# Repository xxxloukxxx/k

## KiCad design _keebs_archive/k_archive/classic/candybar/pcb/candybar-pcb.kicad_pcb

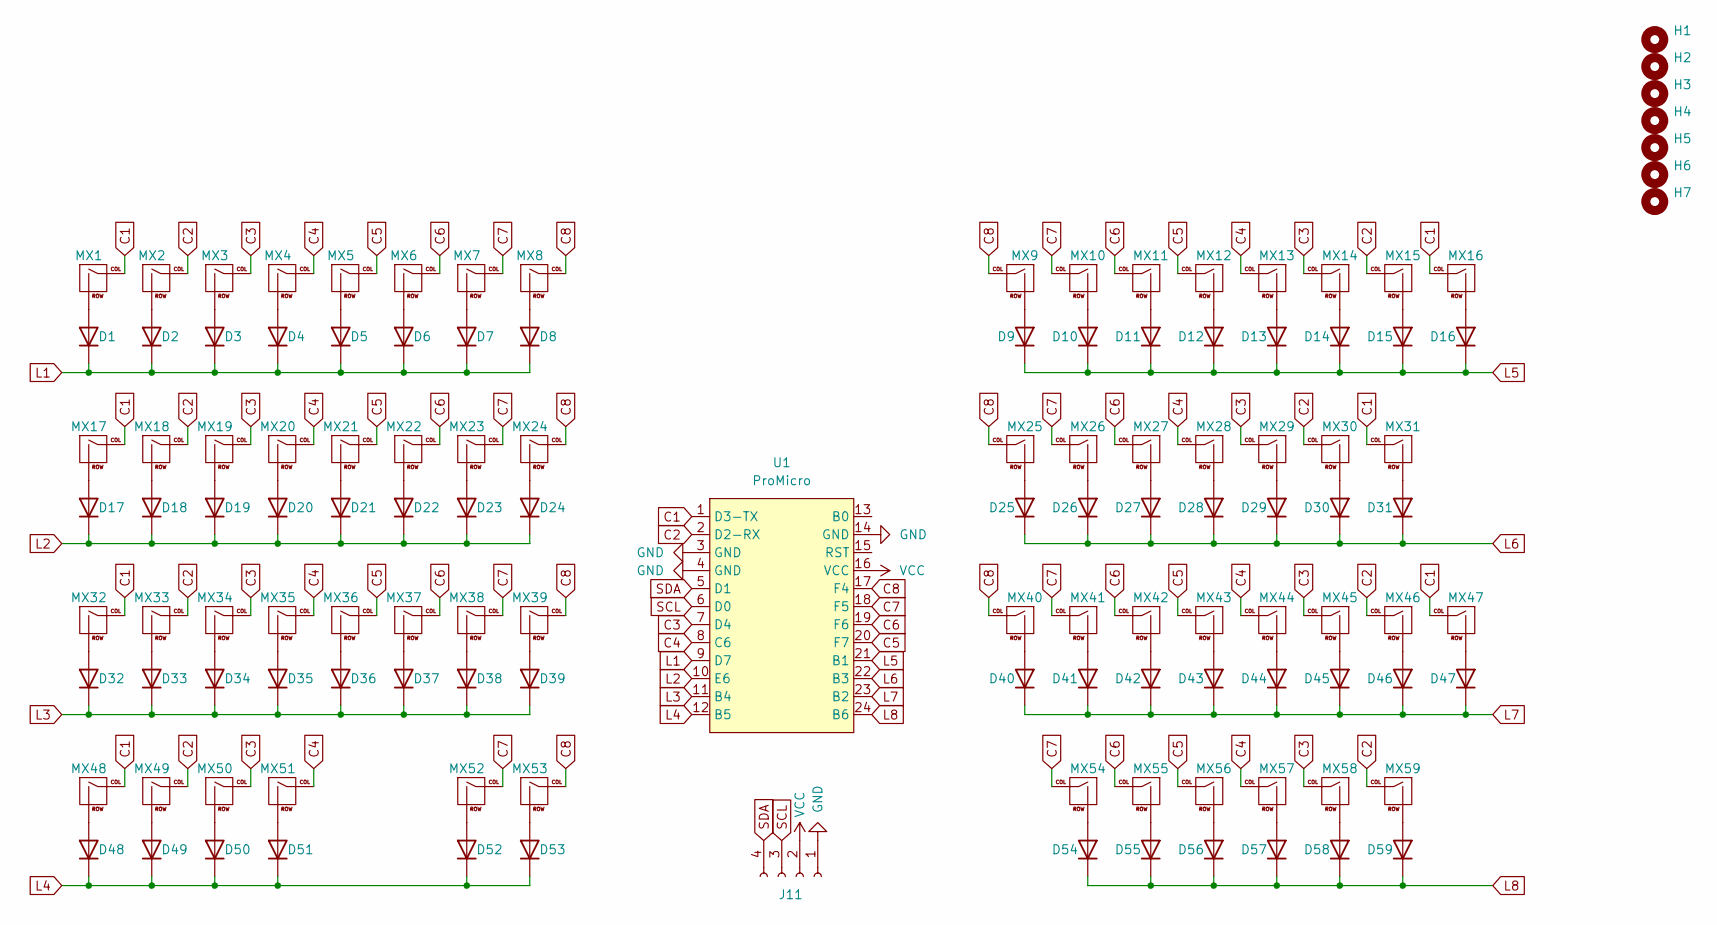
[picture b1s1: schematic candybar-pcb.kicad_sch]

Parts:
D1, D2, D3, D4, D5, D6, D7, D8, D9, D10, D11, D12, D13, D14, D15, D16, D17, D18, D19, D20, D21, D22, D23, D24, D25, D26, D27, D28, D29, D30, D31, D32, D33, D34, D35, D36, D37, D38, D39, D40, D41, D42, D43, D44, D45, D46, D47, D48, D49, D50, D51, D52, D53, D54, D55, D56, D57, D58, D59: 1N4148; D_DO-35_SOD27_P7.62mm_Horizontal
H1, H2, H3, H4, H5, H6, H7: MountingHole; MountingHole_2.2mm_M2
J11: Conn_01x04_Socket; SSD1306-0.91-OLED-4pin-128x32
MX1, MX2, MX3, MX4, MX5, MX6, MX7, MX8, MX9, MX10, MX11, MX12, MX13, MX14, MX15, MX16, MX18, MX19, MX20, MX21, MX22, MX23, MX24, MX25, MX26, MX28, MX29, MX30, MX31, MX33, MX34, MX35, MX36, MX37, MX38, MX39, MX40, MX41, MX43, MX44, MX45, MX46, MX49, MX55, MX56, MX57, MX58, MX59: MX; MX-Alps-Hybrid-1U
MX17, MX42, MX48, MX50, MX53, MX54: MX; MX-Alps-Hybrid-1.25U
MX27, MX32: MX; MX-Alps-Hybrid-1.75U
MX47: MX; MX-Alps-Hybrid-2U-Vertical
MX51: MX; MX-Alps-Hybrid-2.75U-ReversedStabilizers
MX52: MX; MX-Alps-Hybrid-2.25U-ReversedStabilizers
U1: ProMicro; ProMicro_USBup

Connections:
C1: MX1.1 (COL), MX16.1 (COL), MX17.1 (COL), MX31.1 (COL), MX32.1 (COL), MX47.1 (COL), MX48.1 (COL), U1.1 (D3-TX)
C2: MX2.1 (COL), MX15.1 (COL), MX18.1 (COL), MX30.1 (COL), MX33.1 (COL), MX46.1 (COL), MX49.1 (COL), MX59.1 (COL), U1.2 (D2-RX)
C3: MX3.1 (COL), MX14.1 (COL), MX19.1 (COL), MX29.1 (COL), MX34.1 (COL), MX45.1 (COL), MX50.1 (COL), MX58.1 (COL), U1.7 (D4)
C4: MX4.1 (COL), MX13.1 (COL), MX20.1 (COL), MX28.1 (COL), MX35.1 (COL), MX44.1 (COL), MX51.1 (COL), MX57.1 (COL), U1.8 (C6)
C5: MX5.1 (COL), MX12.1 (COL), MX21.1 (COL), MX36.1 (COL), MX43.1 (COL), MX56.1 (COL), U1.20 (F7)
C6: MX6.1 (COL), MX11.1 (COL), MX22.1 (COL), MX27.1 (COL), MX37.1 (COL), MX42.1 (COL), MX55.1 (COL), U1.19 (F6)
C7: MX7.1 (COL), MX10.1 (COL), MX23.1 (COL), MX26.1 (COL), MX38.1 (COL), MX41.1 (COL), MX52.1 (COL), MX54.1 (COL), U1.18 (F5)
C8: MX8.1 (COL), MX9.1 (COL), MX24.1 (COL), MX25.1 (COL), MX39.1 (COL), MX40.1 (COL), MX53.1 (COL), U1.17 (F4)
GND: J11.1, U1.3 (GND), U1.4 (GND), U1.14 (GND)
L1: D1.1 (K), D2.1 (K), D3.1 (K), D4.1 (K), D5.1 (K), D6.1 (K), D7.1 (K), D8.1 (K), U1.9 (D7)
L2: D17.1 (K), D18.1 (K), D19.1 (K), D20.1 (K), D21.1 (K), D22.1 (K), D23.1 (K), D24.1 (K), U1.10 (E6)
L3: D32.1 (K), D33.1 (K), D34.1 (K), D35.1 (K), D36.1 (K), D37.1 (K), D38.1 (K), D39.1 (K), U1.11 (B4)
L4: D48.1 (K), D49.1 (K), D50.1 (K), D51.1 (K), D52.1 (K), D53.1 (K), U1.12 (B5)
L5: D9.1 (K), D10.1 (K), D11.1 (K), D12.1 (K), D13.1 (K), D14.1 (K), D15.1 (K), D16.1 (K), U1.21 (B1)
L6: D25.1 (K), D26.1 (K), D27.1 (K), D28.1 (K), D29.1 (K), D30.1 (K), D31.1 (K), U1.22 (B3)
L7: D40.1 (K), D41.1 (K), D42.1 (K), D43.1 (K), D44.1 (K), D45.1 (K), D46.1 (K), D47.1 (K), U1.23 (B2)
L8: D54.1 (K), D55.1 (K), D56.1 (K), D57.1 (K), D58.1 (K), D59.1 (K), U1.24 (B6)
unnamed: D1.2 (A), MX1.2 (ROW)
unnamed: D2.2 (A), MX2.2 (ROW)
unnamed: D3.2 (A), MX3.2 (ROW)
unnamed: D4.2 (A), MX4.2 (ROW)
unnamed: D5.2 (A), MX5.2 (ROW)
unnamed: D6.2 (A), MX6.2 (ROW)
unnamed: D7.2 (A), MX7.2 (ROW)
unnamed: D8.2 (A), MX8.2 (ROW)
unnamed: D9.2 (A), MX9.2 (ROW)
unnamed: D10.2 (A), MX10.2 (ROW)
unnamed: D11.2 (A), MX11.2 (ROW)
unnamed: D12.2 (A), MX12.2 (ROW)
unnamed: D13.2 (A), MX13.2 (ROW)
unnamed: D14.2 (A), MX14.2 (ROW)
unnamed: D15.2 (A), MX15.2 (ROW)
unnamed: D16.2 (A), MX16.2 (ROW)
unnamed: D17.2 (A), MX17.2 (ROW)
unnamed: D18.2 (A), MX18.2 (ROW)
unnamed: D19.2 (A), MX19.2 (ROW)
unnamed: D20.2 (A), MX20.2 (ROW)
unnamed: D21.2 (A), MX21.2 (ROW)
unnamed: D22.2 (A), MX22.2 (ROW)
unnamed: D23.2 (A), MX23.2 (ROW)
unnamed: D24.2 (A), MX24.2 (ROW)
unnamed: D25.2 (A), MX25.2 (ROW)
unnamed: D26.2 (A), MX26.2 (ROW)
unnamed: D27.2 (A), MX27.2 (ROW)
unnamed: D28.2 (A), MX28.2 (ROW)
unnamed: D29.2 (A), MX29.2 (ROW)
unnamed: D30.2 (A), MX30.2 (ROW)
unnamed: D31.2 (A), MX31.2 (ROW)
unnamed: D32.2 (A), MX32.2 (ROW)
unnamed: D33.2 (A), MX33.2 (ROW)
unnamed: D34.2 (A), MX34.2 (ROW)
unnamed: D35.2 (A), MX35.2 (ROW)
unnamed: D36.2 (A), MX36.2 (ROW)
unnamed: D37.2 (A), MX37.2 (ROW)
unnamed: D38.2 (A), MX38.2 (ROW)
unnamed: D39.2 (A), MX39.2 (ROW)
unnamed: D40.2 (A), MX40.2 (ROW)
unnamed: D41.2 (A), MX41.2 (ROW)
unnamed: D42.2 (A), MX42.2 (ROW)
unnamed: D43.2 (A), MX43.2 (ROW)
unnamed: D44.2 (A), MX44.2 (ROW)
unnamed: D45.2 (A), MX45.2 (ROW)
unnamed: D46.2 (A), MX46.2 (ROW)
unnamed: D47.2 (A), MX47.2 (ROW)
unnamed: D48.2 (A), MX48.2 (ROW)
unnamed: D49.2 (A), MX49.2 (ROW)
unnamed: D50.2 (A), MX50.2 (ROW)
unnamed: D51.2 (A), MX51.2 (ROW)
unnamed: D52.2 (A), MX52.2 (ROW)
unnamed: D53.2 (A), MX53.2 (ROW)
unnamed: D54.2 (A), MX54.2 (ROW)
unnamed: D55.2 (A), MX55.2 (ROW)
unnamed: D56.2 (A), MX56.2 (ROW)
unnamed: D57.2 (A), MX57.2 (ROW)
unnamed: D58.2 (A), MX58.2 (ROW)
unnamed: D59.2 (A), MX59.2 (ROW)
SCL: J11.3, U1.6 (D0)
SDA: J11.4, U1.5 (D1)
VCC: J11.2, U1.16 (VCC)

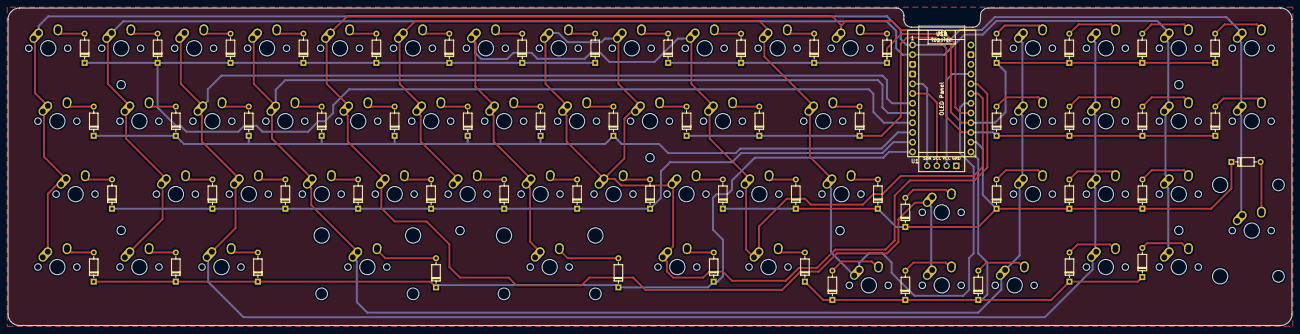
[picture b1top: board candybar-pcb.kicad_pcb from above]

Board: 2 copper layers, 335.3 x 82.9 mm, 127 parts (0 on the bottom side), 79 nets.

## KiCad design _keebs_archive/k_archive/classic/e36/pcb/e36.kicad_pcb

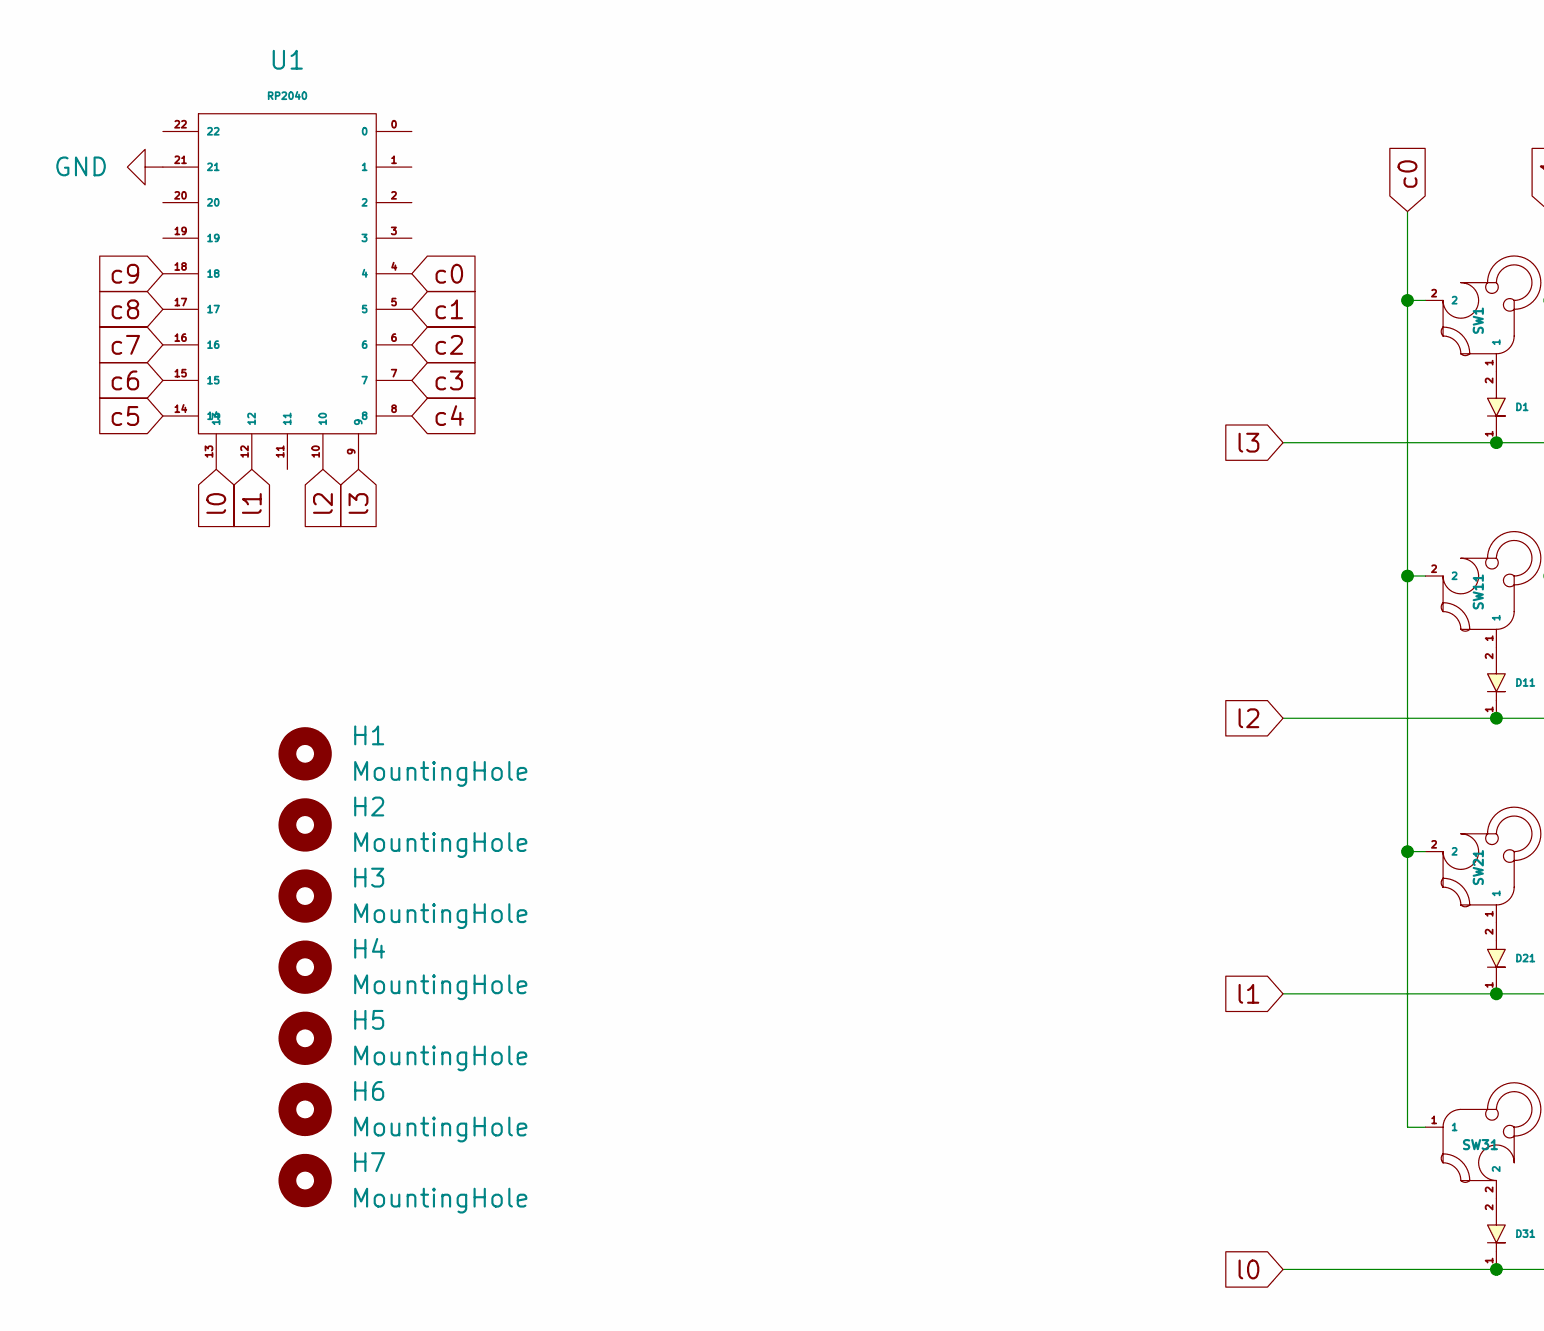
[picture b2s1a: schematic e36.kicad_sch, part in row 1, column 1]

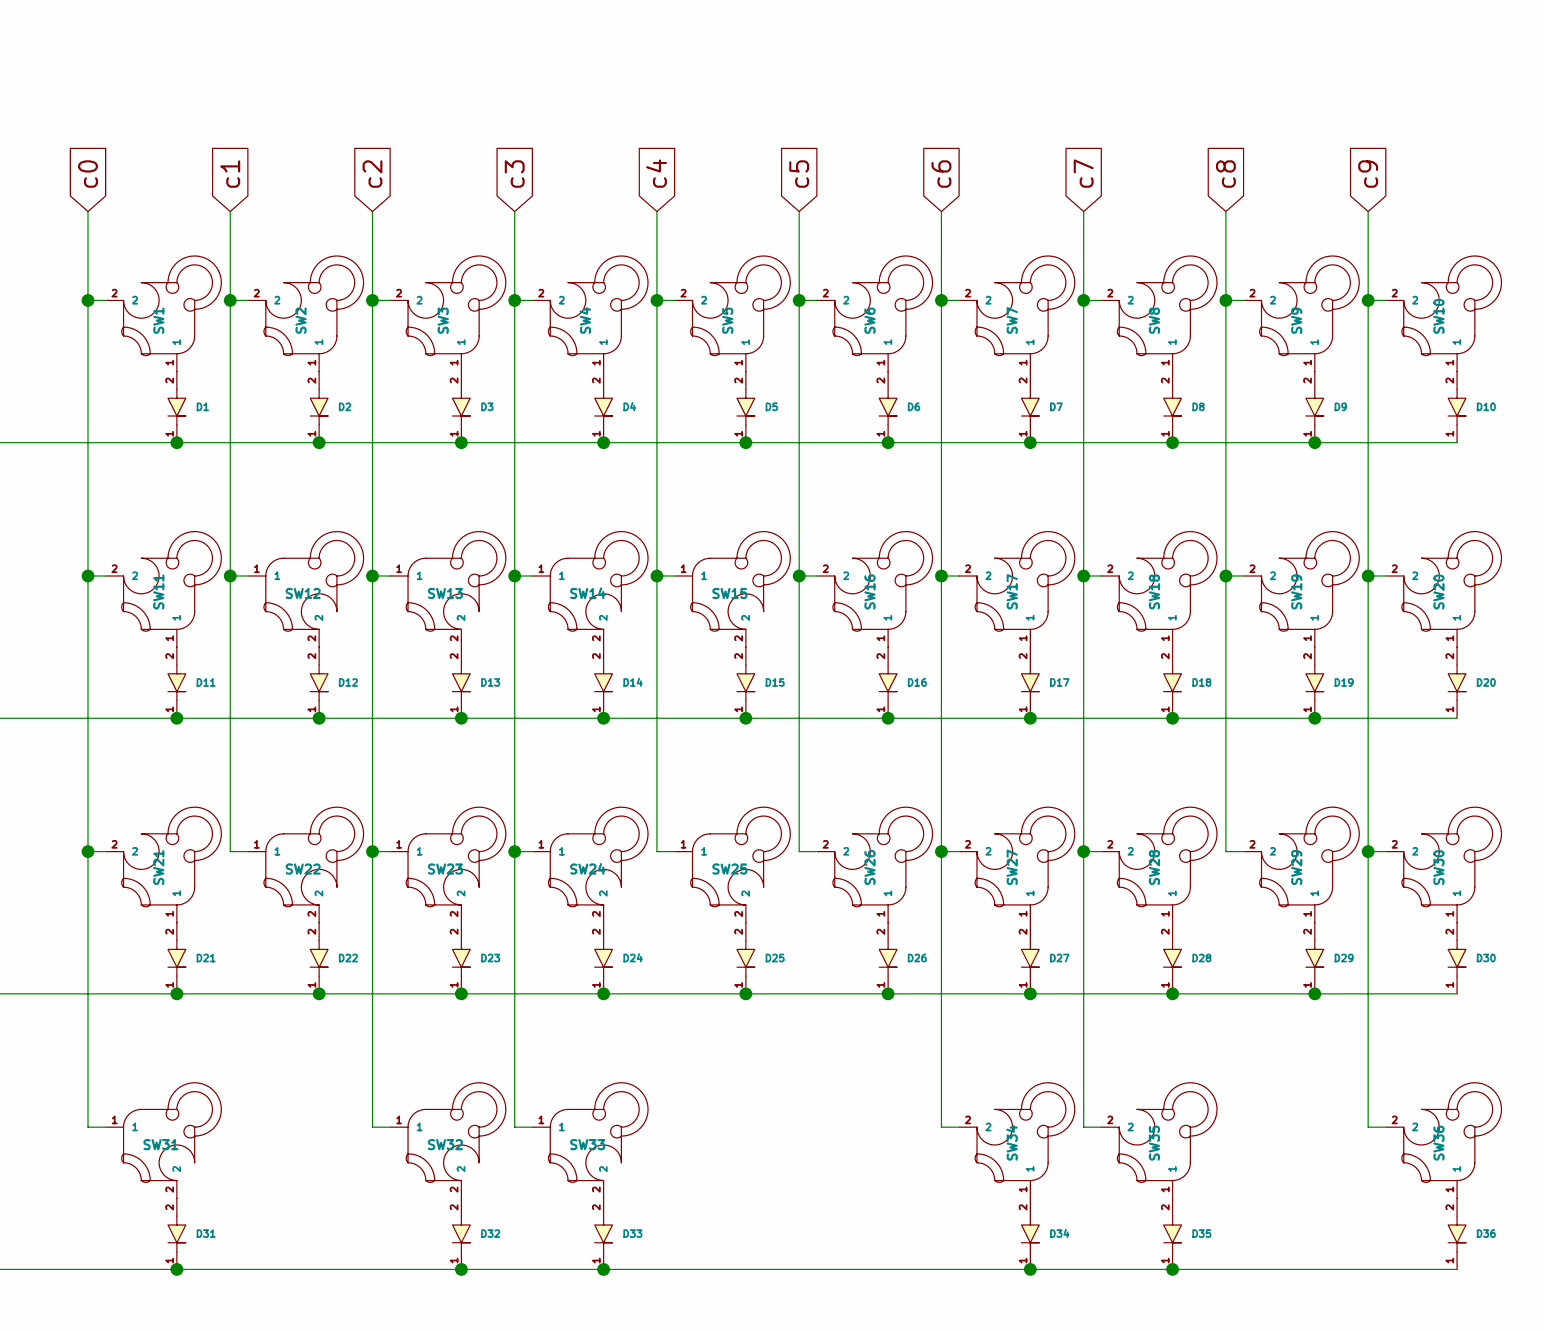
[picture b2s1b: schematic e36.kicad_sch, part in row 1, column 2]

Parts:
D1, D2, D3, D4, D5, D6, D7, D8, D9, D10, D11, D12, D13, D14, D15, D16, D17, D18, D19, D20, D21, D22, D23, D24, D25, D26, D27, D28, D29, D30, D31, D32, D33, D34, D35, D36: Diode
H1, H2, H3, H4, H5, H6, H7: MountingHole; MountingHole_2.2mm_M2
SW1, SW2, SW3, SW4, SW5, SW6, SW7, SW8, SW9, SW10, SW11, SW12, SW13, SW14, SW15, SW16, SW17, SW18, SW19, SW20, SW21, SW22, SW23, SW24, SW25, SW26, SW27, SW28, SW29, SW30, SW31, SW32, SW35, SW36: key; MX-5pin
SW33, SW34: key; MX-5pin_stab
U1: RP2040

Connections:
GND: U1.21
unnamed: D1.2, SW1.1
unnamed: D2.2, SW2.1
unnamed: D3.2, SW3.1
unnamed: D4.2, SW4.1
unnamed: D5.2, SW5.1
unnamed: D6.2, SW6.1
unnamed: D7.2, SW7.1
unnamed: D8.2, SW8.1
unnamed: D9.2, SW9.1
unnamed: D10.2, SW10.1
unnamed: D11.2, SW11.1
unnamed: D12.2, SW12.2
unnamed: D13.2, SW13.2
unnamed: D14.2, SW14.2
unnamed: D15.2, SW15.2
unnamed: D16.2, SW16.1
unnamed: D17.2, SW17.1
unnamed: D18.2, SW18.1
unnamed: D19.2, SW19.1
unnamed: D20.2, SW20.1
unnamed: D21.2, SW21.1
unnamed: D22.2, SW22.2
unnamed: D23.2, SW23.2
unnamed: D24.2, SW24.2
unnamed: D25.2, SW25.2
unnamed: D26.2, SW26.1
unnamed: D27.2, SW27.1
unnamed: D28.2, SW28.1
unnamed: D29.2, SW29.1
unnamed: D30.2, SW30.1
unnamed: D31.2, SW31.2
unnamed: D32.2, SW32.2
unnamed: D33.2, SW33.2
unnamed: D34.2, SW34.1
unnamed: D35.2, SW35.1
unnamed: D36.2, SW36.1
c0: SW1.2, SW11.2, SW21.2, SW31.1, U1.4
c1: SW2.2, SW12.1, SW22.1, U1.5
c2: SW3.2, SW13.1, SW23.1, SW32.1, U1.6
c3: SW4.2, SW14.1, SW24.1, SW33.1, U1.7
c4: SW5.2, SW15.1, SW25.1, U1.8
c5: SW6.2, SW16.2, SW26.2, U1.14
c6: SW7.2, SW17.2, SW27.2, SW34.2, U1.15
c7: SW8.2, SW18.2, SW28.2, SW35.2, U1.16
c8: SW9.2, SW19.2, SW29.2, U1.17
c9: SW10.2, SW20.2, SW30.2, SW36.2, U1.18
l0: D31.1, D32.1, D33.1, D34.1, D35.1, D36.1, U1.13
l1: D21.1, D22.1, D23.1, D24.1, D25.1, D26.1, D27.1, D28.1, D29.1, D30.1, U1.12
l2: D11.1, D12.1, D13.1, D14.1, D15.1, D16.1, D17.1, D18.1, D19.1, D20.1, U1.10
l3: D1.1, D2.1, D3.1, D4.1, D5.1, D6.1, D7.1, D8.1, D9.1, D10.1, U1.9

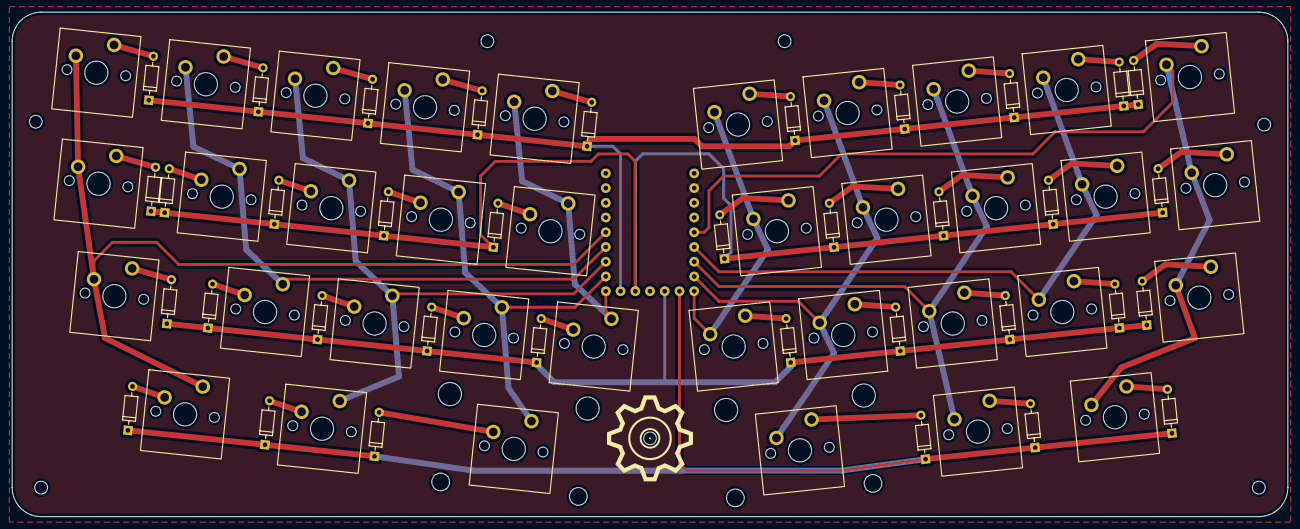
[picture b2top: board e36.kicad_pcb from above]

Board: 2 copper layers, 220.0 x 87.0 mm, 80 parts (1 on the bottom side), 50 nets.

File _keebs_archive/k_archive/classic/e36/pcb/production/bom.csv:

Designator,Footprint,Quantity,Value,LCSC Part #
"D1, D10, D11, D12, D13, D14, D15, D16, D17, D18, D19, D2, D20, D21, D22, D23, D24, D25, D26, D27, D28, D29, D3, D30, D31, D32, D33, D34, D35, D36, D4, D5, D6, D7, D8, D9",Diode,36,Diode,
"H1, H2, H3, H4, H5, H6, H7",MountingHole_2.2mm_M2,7,MountingHole,
"SW1, SW10, SW11, SW12, SW13, SW14, SW15, SW16, SW17, SW18, SW19, SW2, SW20, SW21, SW22, SW23, SW24, SW25, SW26, SW27, SW28, SW29, SW3, SW30, SW31, SW32, SW35, SW36, SW4, SW5, SW6, SW7, SW8, SW9",MX-5pin,34,key,
"SW33, SW34",MX-5pin_stab,2,key,
U1,RP2040,1,RP2040,

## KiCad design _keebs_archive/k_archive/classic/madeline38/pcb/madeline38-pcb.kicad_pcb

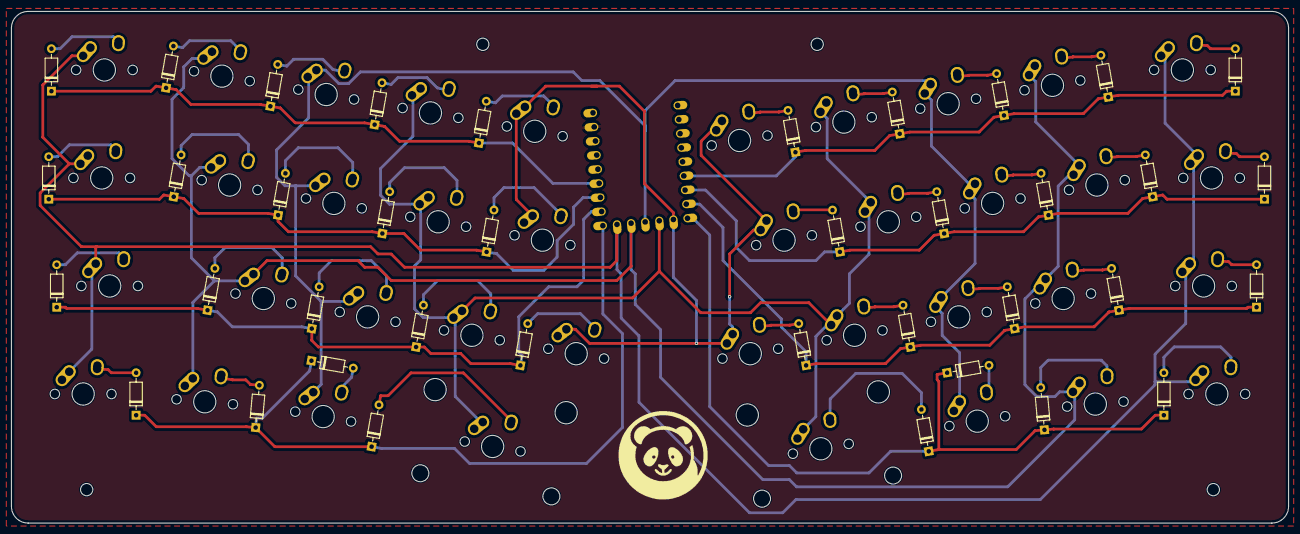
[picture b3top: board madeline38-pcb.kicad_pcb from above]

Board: 2 copper layers, 229.1 x 91.8 mm, 81 parts (0 on the bottom side), 51 nets.

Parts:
D1, D2, D3, D4, D5, D6, D7, D8, D9, D10, D11, D12, D13, D14, D15, D16, D17, D18, D19, D20, D21, D22, D23, D24, D25, D26, D27, D28, D29, D30, D31, D32, D33, D34, D35, D36, D37, D38: 1N4148; D_DO-35_SOD27_P7.62mm_Horizontal
H1, H2, H3, H4: MountingHole; MountingHole_2.2mm_M2
SW1, SW2, SW3, SW4, SW5, SW6, SW7, SW8, SW9, SW12, SW13, SW14, SW15, SW16, SW17, SW18, SW19, SW20, SW22, SW23, SW24, SW25, SW26, SW27, SW28, SW29, SW31, SW32, SW33, SW36, SW37, SW38: SW_SPST; MX-Alps-Hybrid-1U
SW10, SW11: SW_SPST; MX-Alps-Hybrid-1.25U
SW21: SW_SPST; MX-Alps-Hybrid-1.75U
SW30: SW_SPST; MX-Alps-Hybrid-1.5U
SW34: SW_SPST; MX-Alps-Hybrid-2.25U-ReversedStabilizers
SW35: SW_SPST; MX-Alps-Hybrid-2U-ReversedStabilizers
U1: rp2040-zero; rp2040-zero-tht

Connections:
unnamed: D1.2 (A), SW1.2 (B)
unnamed: D2.2 (A), SW2.2 (B)
unnamed: D3.2 (A), SW3.2 (B)
unnamed: D4.2 (A), SW4.2 (B)
unnamed: D5.2 (A), SW5.2 (B)
unnamed: D6.2 (A), SW6.2 (B)
unnamed: D7.2 (A), SW7.2 (B)
unnamed: D8.2 (A), SW8.2 (B)
unnamed: D9.2 (A), SW9.2 (B)
unnamed: D10.2 (A), SW10.2 (B)
unnamed: D11.2 (A), SW11.2 (B)
unnamed: D12.2 (A), SW12.2 (B)
unnamed: D13.2 (A), SW13.2 (B)
unnamed: D14.2 (A), SW14.2 (B)
unnamed: D15.2 (A), SW15.2 (B)
unnamed: D16.2 (A), SW16.2 (B)
unnamed: D17.2 (A), SW17.2 (B)
unnamed: D18.2 (A), SW18.2 (B)
unnamed: D19.2 (A), SW19.2 (B)
unnamed: D20.2 (A), SW20.2 (B)
unnamed: D21.2 (A), SW21.2 (B)
unnamed: D22.2 (A), SW22.2 (B)
unnamed: D23.2 (A), SW23.2 (B)
unnamed: D24.2 (A), SW24.2 (B)
unnamed: D25.2 (A), SW25.2 (B)
unnamed: D26.2 (A), SW26.2 (B)
unnamed: D27.2 (A), SW27.2 (B)
unnamed: D28.2 (A), SW28.2 (B)
unnamed: D29.2 (A), SW29.2 (B)
unnamed: D30.2 (A), SW30.2 (B)
unnamed: D31.2 (A), SW31.2 (B)
unnamed: D32.2 (A), SW32.2 (B)
unnamed: D33.2 (A), SW33.2 (B)
unnamed: D34.2 (A), SW34.2 (B)
unnamed: D35.2 (A), SW35.2 (B)
unnamed: D36.2 (A), SW36.2 (B)
unnamed: D37.2 (A), SW37.2 (B)
unnamed: D38.2 (A), SW38.2 (B)
c0: SW1.1 (A), SW10.1 (A), SW11.1 (A), SW20.1 (A), SW21.1 (A), SW30.1 (A), SW31.1 (A), SW38.1 (A), U1.14 (13)
c1: SW2.1 (A), SW9.1 (A), SW12.1 (A), SW19.1 (A), SW22.1 (A), SW29.1 (A), SW32.1 (A), SW37.1 (A), U1.13 (12)
c2: SW3.1 (A), SW8.1 (A), SW13.1 (A), SW18.1 (A), SW23.1 (A), SW28.1 (A), SW33.1 (A), SW36.1 (A), U1.12 (11)
c3: SW4.1 (A), SW7.1 (A), SW14.1 (A), SW17.1 (A), SW24.1 (A), SW27.1 (A), SW34.1 (A), SW35.1 (A), U1.11 (10)
c4: SW5.1 (A), SW6.1 (A), SW15.1 (A), SW16.1 (A), SW25.1 (A), SW26.1 (A), U1.10 (9)
l0: D1.1 (K), D2.1 (K), D3.1 (K), D4.1 (K), D5.1 (K), U1.18 (27)
l1: D11.1 (K), D12.1 (K), D13.1 (K), D14.1 (K), D15.1 (K), U1.17 (26)
l2: D21.1 (K), D22.1 (K), D23.1 (K), D24.1 (K), D25.1 (K), U1.16 (15)
l3: D31.1 (K), D32.1 (K), D33.1 (K), D34.1 (K), U1.15 (14)
l4: D35.1 (K), D36.1 (K), D37.1 (K), D38.1 (K), U1.9 (8)
l5: D26.1 (K), D27.1 (K), D28.1 (K), D29.1 (K), D30.1 (K), U1.8 (7)
l6: D16.1 (K), D17.1 (K), D18.1 (K), D19.1 (K), D20.1 (K), U1.7 (6)
l7: D6.1 (K), D7.1 (K), D8.1 (K), D9.1 (K), D10.1 (K), U1.6 (5)

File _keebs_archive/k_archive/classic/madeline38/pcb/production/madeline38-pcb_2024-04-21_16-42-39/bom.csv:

Designator,Footprint,Quantity,Value,LCSC Part #
"D1, D10, D11, D12, D13, D14, D15, D16, D17, D18, D19, D2, D20, D21, D22, D23, D24, D25, D26, D27, D28, D29, D3, D30, D31, D32, D33, D34, D35, D36, D37, D38, D4, D5, D6, D7, D8, D9",D_DO-35_SOD27_P7.62mm_Horizontal,38,1N4148,
"H1, H2, H3, H4",MountingHole_2.2mm_M2,4,MountingHole,
"SW1, SW12, SW13, SW14, SW15, SW16, SW17, SW18, SW19, SW2, SW20, SW22, SW23, SW24, SW25, SW26, SW27, SW28, SW29, SW3, SW31, SW32, SW33, SW36, SW37, SW38, SW4, SW5, SW6, SW7, SW8, SW9",MX-Alps-Hybrid-1U,32,SW_SPST,
"SW10, SW11",MX-Alps-Hybrid-1.25U,2,SW_SPST,
SW21,MX-Alps-Hybrid-1.75U,1,SW_SPST,
SW30,MX-Alps-Hybrid-1.5U,1,SW_SPST,
SW34,MX-Alps-Hybrid-2.25U-ReversedStabilizers,1,SW_SPST,
SW35,MX-Alps-Hybrid-2U-ReversedStabilizers,1,SW_SPST,
U1,rp2040-zero-tht,1,rp2040-zero,

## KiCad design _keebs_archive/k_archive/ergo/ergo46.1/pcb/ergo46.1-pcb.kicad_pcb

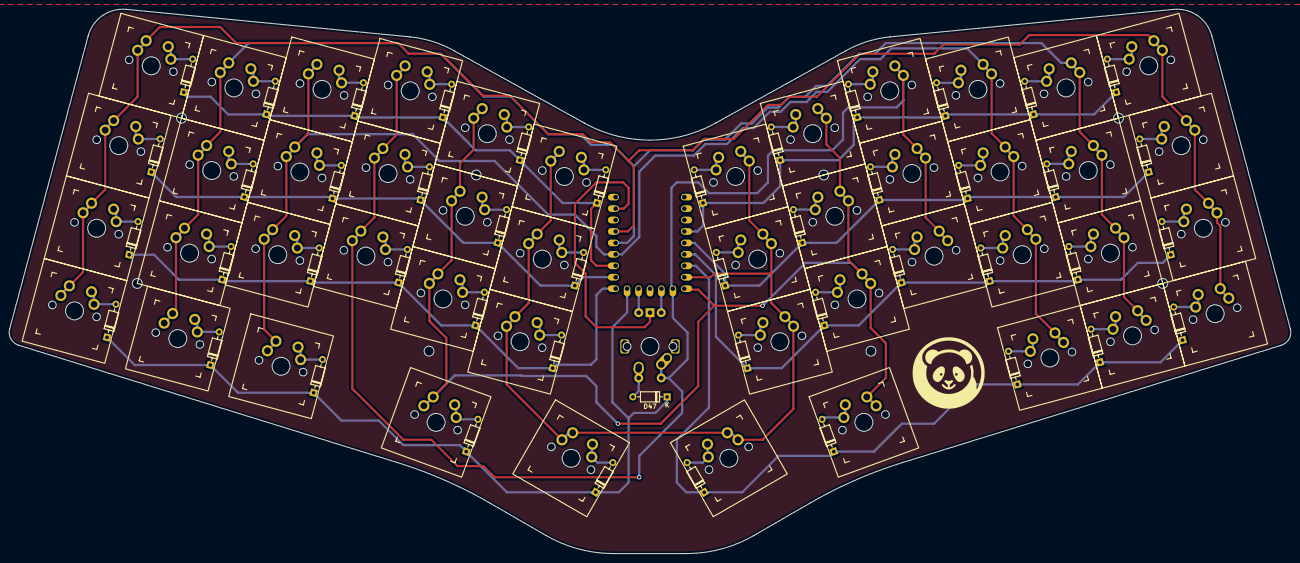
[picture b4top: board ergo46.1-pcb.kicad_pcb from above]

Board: 2 copper layers, 284.6 x 120.9 mm, 103 parts (0 on the bottom side), 64 nets.

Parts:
D1, D2, D3, D4, D5, D6, D7, D8, D9, D10, D11, D12, D13, D14, D15, D16, D17, D18, D19, D20, D21, D22, D23, D24, D25, D26, D27, D28, D29, D30, D31, D32, D33, D34, D35, D36, D37, D38, D39, D40, D41, D42, D43, D44, D45, D46, D47: 1N4148; D_DO-35_SOD27_P7.62mm_Horizontal
H1, H2, H3, H4, H5, H7, H8, H9: MountingHole; MountingHole_2.2mm_M2
MX1, MX2, MX3, MX4, MX5, MX6, MX7, MX8, MX9, MX10, MX11, MX12, MX13, MX14, MX15, MX16, MX17, MX18, MX19, MX20, MX21, MX22, MX23, MX24, MX25, MX26, MX27, MX28, MX29, MX30, MX31, MX32, MX33, MX34, MX35, MX36, MX37, MX38, MX39, MX40, MX41, MX42, MX43, MX44, MX45, MX46: MX; SW_MX_reversible
SW1: EC11-MX-Alps
U1: rp2040-zero; rp2040-zero-tht

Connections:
C0: MX1.1 (COL), MX12.2 (ROW), MX13.1 (COL), MX24.2 (ROW), MX25.1 (COL), MX36.2 (ROW), MX37.1 (COL), MX46.2 (ROW), U1.20 (29)
C1: MX2.1 (COL), MX11.2 (ROW), MX14.1 (COL), MX23.2 (ROW), MX26.1 (COL), MX35.2 (ROW), MX38.1 (COL), MX45.2 (ROW), U1.19 (28)
C2: MX3.1 (COL), MX10.2 (ROW), MX15.1 (COL), MX22.2 (ROW), MX27.1 (COL), MX34.2 (ROW), MX39.1 (COL), MX44.2 (ROW), U1.18 (27)
C3: MX4.1 (COL), MX9.2 (ROW), MX16.1 (COL), MX21.2 (ROW), MX28.1 (COL), MX33.2 (ROW), SW1.1, U1.10 (9)
C4: MX5.1 (COL), MX8.2 (ROW), MX17.1 (COL), MX20.2 (ROW), MX29.1 (COL), MX32.2 (ROW), MX40.1 (COL), MX43.2 (ROW), U1.9 (8)
C5: MX6.1 (COL), MX7.2 (ROW), MX18.1 (COL), MX19.2 (ROW), MX30.1 (COL), MX31.2 (ROW), MX41.1 (COL), MX42.2 (ROW), U1.8 (7)
GND: SW1.C, U1.22 (GND)
L0: D1.1 (K), D2.1 (K), D3.1 (K), D4.1 (K), D5.1 (K), D6.1 (K), U1.17 (26)
L1: D7.1 (K), D8.1 (K), D9.1 (K), D10.1 (K), D11.1 (K), D12.1 (K), U1.4 (3)
L2: D13.1 (K), D14.1 (K), D15.1 (K), D16.1 (K), D17.1 (K), D18.1 (K), U1.16 (15)
L3: D19.1 (K), D20.1 (K), D21.1 (K), D22.1 (K), D23.1 (K), D24.1 (K), U1.5 (4)
L4: D25.1 (K), D26.1 (K), D27.1 (K), D28.1 (K), D29.1 (K), D30.1 (K), U1.15 (14)
L5: D31.1 (K), D32.1 (K), D33.1 (K), D34.1 (K), D35.1 (K), D36.1 (K), U1.6 (5)
L6: D37.1 (K), D38.1 (K), D39.1 (K), D40.1 (K), D41.1 (K), D47.1 (K), U1.14 (13)
L7: D42.1 (K), D43.1 (K), D44.1 (K), D45.1 (K), D46.1 (K), U1.7 (6)
unnamed: D1.2 (A), MX1.2 (ROW)
unnamed: D2.2 (A), MX2.2 (ROW)
unnamed: D3.2 (A), MX3.2 (ROW)
unnamed: D4.2 (A), MX4.2 (ROW)
unnamed: D5.2 (A), MX5.2 (ROW)
unnamed: D6.2 (A), MX6.2 (ROW)
unnamed: D7.2 (A), MX7.1 (COL)
unnamed: D8.2 (A), MX8.1 (COL)
unnamed: D9.2 (A), MX9.1 (COL)
unnamed: D10.2 (A), MX10.1 (COL)
unnamed: D11.2 (A), MX11.1 (COL)
unnamed: D12.2 (A), MX12.1 (COL)
unnamed: D13.2 (A), MX13.2 (ROW)
unnamed: D14.2 (A), MX14.2 (ROW)
unnamed: D15.2 (A), MX15.2 (ROW)
unnamed: D16.2 (A), MX16.2 (ROW)
unnamed: D17.2 (A), MX17.2 (ROW)
unnamed: D18.2 (A), MX18.2 (ROW)
unnamed: D19.2 (A), MX19.1 (COL)
unnamed: D20.2 (A), MX20.1 (COL)
unnamed: D21.2 (A), MX21.1 (COL)
unnamed: D22.2 (A), MX22.1 (COL)
unnamed: D23.2 (A), MX23.1 (COL)
unnamed: D24.2 (A), MX24.1 (COL)
unnamed: D25.2 (A), MX25.2 (ROW)
unnamed: D26.2 (A), MX26.2 (ROW)
unnamed: D27.2 (A), MX27.2 (ROW)
unnamed: D28.2 (A), MX28.2 (ROW)
unnamed: D29.2 (A), MX29.2 (ROW)
unnamed: D30.2 (A), MX30.2 (ROW)
unnamed: D31.2 (A), MX31.1 (COL)
unnamed: D32.2 (A), MX32.1 (COL)
unnamed: D33.2 (A), MX33.1 (COL)
unnamed: D34.2 (A), MX34.1 (COL)
unnamed: D35.2 (A), MX35.1 (COL)
unnamed: D36.2 (A), MX36.1 (COL)
unnamed: D37.2 (A), MX37.2 (ROW)
unnamed: D38.2 (A), MX38.2 (ROW)
unnamed: D39.2 (A), MX39.2 (ROW)
unnamed: D40.2 (A), MX40.2 (ROW)
unnamed: D41.2 (A), MX41.2 (ROW)
unnamed: D42.2 (A), MX42.1 (COL)
unnamed: D43.2 (A), MX43.1 (COL)
unnamed: D44.2 (A), MX44.1 (COL)
unnamed: D45.2 (A), MX45.1 (COL)
unnamed: D46.2 (A), MX46.1 (COL)
unnamed: D47.2 (A), SW1.2
unnamed: SW1.A, U1.11 (10)
unnamed: SW1.B, U1.13 (12)
